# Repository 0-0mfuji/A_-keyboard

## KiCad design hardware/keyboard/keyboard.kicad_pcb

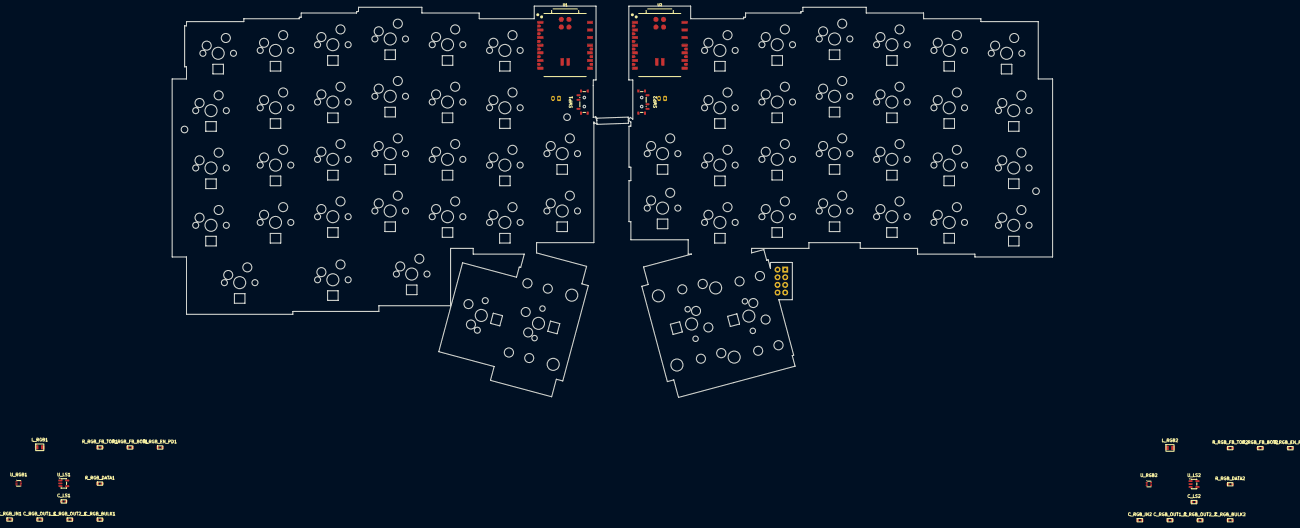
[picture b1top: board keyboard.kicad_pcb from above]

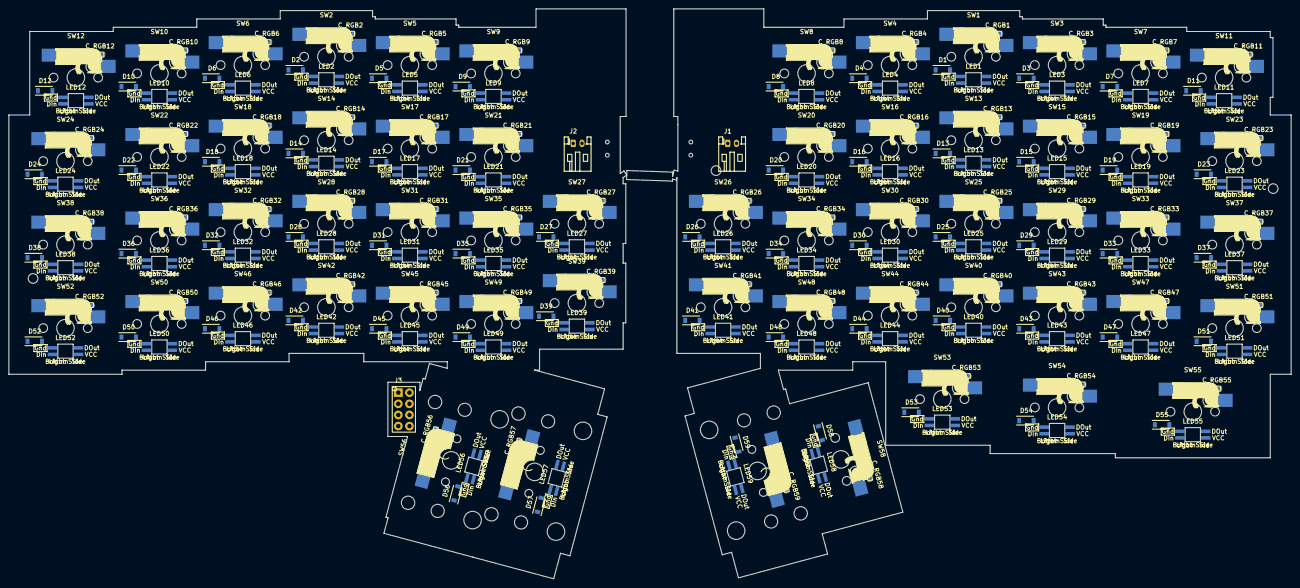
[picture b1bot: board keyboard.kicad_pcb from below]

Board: 2 copper layers, 292.5 x 130.0 mm, 276 parts (180 on the bottom side), 160 nets, no tracks yet.

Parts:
C_LS1, C_LS2: 100nF; C_0603
C_RGB1, C_RGB2, C_RGB3, C_RGB4, C_RGB5, C_RGB6, C_RGB7, C_RGB8, C_RGB9, C_RGB10, C_RGB11, C_RGB12, C_RGB13, C_RGB14, C_RGB15, C_RGB16, C_RGB17, C_RGB18, C_RGB19, C_RGB20, C_RGB21, C_RGB22, C_RGB23, C_RGB24, C_RGB25, C_RGB26, C_RGB27, C_RGB28, C_RGB29, C_RGB30, C_RGB31, C_RGB32, C_RGB33, C_RGB34, C_RGB35, C_RGB36, C_RGB37, C_RGB38, C_RGB39, C_RGB40, C_RGB41, C_RGB42, C_RGB43, C_RGB44, C_RGB45, C_RGB46, C_RGB47, C_RGB48, C_RGB49, C_RGB50, C_RGB51, C_RGB52, C_RGB53, C_RGB54, C_RGB55, C_RGB56, C_RGB57, C_RGB58, C_RGB59: 100nF; C_0603
C_RGB_BULK1, C_RGB_BULK2: 100uF; C_0603
C_RGB_IN1, C_RGB_IN2: 10uF; C_0603
C_RGB_OUT1_1, C_RGB_OUT1_2, C_RGB_OUT2_1, C_RGB_OUT2_2: 22uF; C_0603
D1, D2, D3, D4, D5, D6, D7, D8, D9, D10, D11, D12, D13, D14, D15, D16, D17, D18, D19, D20, D21, D22, D23, D24, D25, D26, D27, D28, D29, D30, D31, D32, D33, D34, D35, D36, D37, D38, D39, D40, D41, D42, D43, D44, D45, D46, D47, D48, D49, D50, D51, D52, D53, D54, D55, D56, D57, D58, D59: 1N4148W; SOD123
H: M2 NPTH clearance; MountingHole
H#2, H#3: M2 NPTH clearance; MountingHole
J1, J2: JST PH 2.0 2-pin; BatteryConnector_JST_PH2
J3: SEIBOKU / jumper wires; SEIBOKU_JUMPER_HEADER
LED1, LED2, LED3, LED4, LED5, LED6, LED7, LED8, LED9, LED10, LED11, LED12, LED13, LED14, LED15, LED16, LED17, LED18, LED19, LED20, LED21, LED22, LED23, LED24, LED25, LED26, LED27, LED28, LED29, LED30, LED31, LED32, LED33, LED34, LED35, LED36, LED37, LED38, LED39, LED40, LED41, LED42, LED43, LED44, LED45, LED46, LED47, LED48, LED49, LED50, LED51, LED52, LED53, LED54, LED55, LED56, LED57, LED58, LED59: SK6812MINI-E; LED_SK6812MINI-E_BL
L_RGB1, L_RGB2: 1uH; L_1008
R_RGB_DATA1, R_RGB_DATA2: 220R; R_0603
R_RGB_EN_PD1, R_RGB_EN_PD2: 100k; R_0603
R_RGB_FB_BOT1, R_RGB_FB_BOT2: 100k; R_0603
R_RGB_FB_TOP1, R_RGB_FB_TOP2: 732k; R_0603
STAB: MX stabilizer NPTH; MXStabilizerHole
STAB#2, STAB#3, STAB#4, STAB#5, STAB#6: MX stabilizer NPTH; MXStabilizerHole
SW1, SW2, SW3, SW4, SW5, SW6, SW7, SW8, SW9, SW10, SW11, SW12, SW13, SW14, SW15, SW16, SW17, SW18, SW19, SW20, SW21, SW22, SW25, SW26, SW27, SW28, SW29, SW30, SW31, SW32, SW33, SW34, SW35, SW36, SW39, SW40, SW41, SW42, SW43, SW44, SW45, SW46, SW47, SW48, SW49, SW50: MX; MX_Hotswap_1u
SW23, SW24, SW37, SW38, SW51, SW52, SW53: MX; MX_Hotswap_1.25u
SW54, SW58: MX; MX_Hotswap_1.5u
SW55: MX; MX_Hotswap_1.75u
SW56: MX; MX_Hotswap_2u
SW57, SW59: MX; MX_Hotswap_2.25u
SWP1, SWP2: MSK-12C02 slide switch; PowerSwitch_MSK12C02
U1, U2: XIAO nRF52840 Plus (SMD); XIAO_NRF52840_PLUS
U_LS1, U_LS2: SN74AHCT1G125
U_RGB1, U_RGB2: TPS61023

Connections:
+3V3_RIGHT: J3.1, U2.12
/COL0: SW1.1, SW8.1, SW16.1, SW25.1, SW33.1, SW41.1, SW48.1, SW55.1, U1.9
/COL1: SW3.1, SW11.1, SW19.1, SW26.1, SW34.1, SW43.1, SW51.1, SW58.1, U1.10
/COL2: SW4.1, SW13.1, SW20.1, SW29.1, SW37.1, SW44.1, SW53.1, SW59.1, U1.11
/COL3: SW7.1, SW15.1, SW23.1, SW30.1, SW40.1, SW47.1, SW54.1, U1.15
/COL4: SW6.1, SW14.1, SW22.1, SW31.1, SW38.1, SW46.1, SW56.1, U2.15
/COL5: SW9.1, SW17.1, SW24.1, SW32.1, SW39.1, SW49.1, SW57.1, U2.16
/COL6: SW2.1, SW10.1, SW18.1, SW27.1, SW35.1, SW42.1, SW50.1, U2.17
/COL7: SW5.1, SW12.1, SW21.1, SW28.1, SW36.1, SW45.1, SW52.1, U2.21
/GND_LEFT: C_LS1.2, C_RGB1.2, C_RGB3.2, C_RGB4.2, C_RGB7.2, C_RGB8.2, C_RGB11.2, C_RGB13.2, C_RGB15.2, C_RGB16.2, C_RGB19.2, C_RGB20.2, C_RGB23.2, C_RGB25.2, C_RGB26.2, C_RGB29.2, C_RGB30.2, C_RGB33.2, C_RGB34.2, C_RGB37.2, C_RGB40.2, C_RGB41.2, C_RGB43.2, C_RGB44.2, C_RGB47.2, C_RGB48.2, C_RGB51.2, C_RGB53.2, C_RGB54.2, C_RGB55.2, C_RGB58.2, C_RGB59.2, C_RGB_BULK1.2, C_RGB_IN1.2, C_RGB_OUT1_1.2, C_RGB_OUT2_1.2, J1.2, LED1.2, LED3.2, LED4.2, LED7.2, LED8.2, LED11.2, LED13.2, LED15.2, LED16.2, LED19.2, LED20.2, LED23.2, LED25.2, LED26.2, LED29.2, LED30.2, LED33.2, LED34.2, LED37.2, LED40.2, LED41.2, LED43.2, LED44.2, LED47.2, LED48.2, LED51.2, LED53.2, LED54.2, LED55.2, LED58.2, LED59.2, R_RGB_EN_PD1.2, R_RGB_FB_BOT1.2, U1.13, U1.27, U1.29, U_LS1.1, U_LS1.3, U_RGB1.4
/GND_RIGHT: C_LS2.2, C_RGB2.2, C_RGB5.2, C_RGB6.2, C_RGB9.2, C_RGB10.2, C_RGB12.2, C_RGB14.2, C_RGB17.2, C_RGB18.2, C_RGB21.2, C_RGB22.2, C_RGB24.2, C_RGB27.2, C_RGB28.2, C_RGB31.2, C_RGB32.2, C_RGB35.2, C_RGB36.2, C_RGB38.2, C_RGB39.2, C_RGB42.2, C_RGB45.2, C_RGB46.2, C_RGB49.2, C_RGB50.2, C_RGB52.2, C_RGB56.2, C_RGB57.2, C_RGB_BULK2.2, C_RGB_IN2.2, C_RGB_OUT1_2.2, C_RGB_OUT2_2.2, J2.2, J3.2, LED2.2, LED5.2, LED6.2, LED9.2, LED10.2, LED12.2, LED14.2, LED17.2, LED18.2, LED21.2, LED22.2, LED24.2, LED27.2, LED28.2, LED31.2, LED32.2, LED35.2, LED36.2, LED38.2, LED39.2, LED42.2, LED45.2, LED46.2, LED49.2, LED50.2, LED52.2, LED56.2, LED57.2, R_RGB_EN_PD2.2, R_RGB_FB_BOT2.2, U2.13, U2.27, U2.29, U_LS2.1, U_LS2.3, U_RGB2.4
/RGB_5V_LEFT: C_LS1.1, C_RGB1.1, C_RGB3.1, C_RGB4.1, C_RGB7.1, C_RGB8.1, C_RGB11.1, C_RGB13.1, C_RGB15.1, C_RGB16.1, C_RGB19.1, C_RGB20.1, C_RGB23.1, C_RGB25.1, C_RGB26.1, C_RGB29.1, C_RGB30.1, C_RGB33.1, C_RGB34.1, C_RGB37.1, C_RGB40.1, C_RGB41.1, C_RGB43.1, C_RGB44.1, C_RGB47.1, C_RGB48.1, C_RGB51.1, C_RGB53.1, C_RGB54.1, C_RGB55.1, C_RGB58.1, C_RGB59.1, C_RGB_BULK1.1, C_RGB_OUT1_1.1, C_RGB_OUT2_1.1, LED1.1, LED3.1, LED4.1, LED7.1, LED8.1, LED11.1, LED13.1, LED15.1, LED16.1, LED19.1, LED20.1, LED23.1, LED25.1, LED26.1, LED29.1, LED30.1, LED33.1, LED34.1, LED37.1, LED40.1, LED41.1, LED43.1, LED44.1, LED47.1, LED48.1, LED51.1, LED53.1, LED54.1, LED55.1, LED58.1, LED59.1, R_RGB_FB_TOP1.1, U_LS1.5, U_RGB1.6
/RGB_5V_RIGHT: C_LS2.1, C_RGB2.1, C_RGB5.1, C_RGB6.1, C_RGB9.1, C_RGB10.1, C_RGB12.1, C_RGB14.1, C_RGB17.1, C_RGB18.1, C_RGB21.1, C_RGB22.1, C_RGB24.1, C_RGB27.1, C_RGB28.1, C_RGB31.1, C_RGB32.1, C_RGB35.1, C_RGB36.1, C_RGB38.1, C_RGB39.1, C_RGB42.1, C_RGB45.1, C_RGB46.1, C_RGB49.1, C_RGB50.1, C_RGB52.1, C_RGB56.1, C_RGB57.1, C_RGB_BULK2.1, C_RGB_OUT1_2.1, C_RGB_OUT2_2.1, LED2.1, LED5.1, LED6.1, LED9.1, LED10.1, LED12.1, LED14.1, LED17.1, LED18.1, LED21.1, LED22.1, LED24.1, LED27.1, LED28.1, LED31.1, LED32.1, LED35.1, LED36.1, LED38.1, LED39.1, LED42.1, LED45.1, LED46.1, LED49.1, LED50.1, LED52.1, LED56.1, LED57.1, R_RGB_FB_TOP2.1, U_LS2.5, U_RGB2.6
/RGB_DATA_LEFT: U1.16, U_LS1.2
/RGB_DATA_RIGHT: U2.22, U_LS2.2
/RGB_DATA_SHIFTED_LEFT: LED1.3, R_RGB_DATA1.2
/RGB_DATA_SHIFTED_RIGHT: LED2.3, R_RGB_DATA2.2
/RGB_EN_LEFT: R_RGB_EN_PD1.1, U1.17, U_RGB1.2
/RGB_EN_RIGHT: R_RGB_EN_PD2.1, U2.23, U_RGB2.2
/ROW0: D1.1, D3.1, D4.1, D7.1, U1.1
/ROW1: D8.1, D11.1, D13.1, D15.1, U1.2
/ROW2: D16.1, D19.1, D20.1, D23.1, U1.3
/ROW3: D25.1, D26.1, D29.1, D30.1, U1.4
/ROW4: D33.1, D34.1, D37.1, D40.1, U1.5
/ROW5: D41.1, D43.1, D44.1, D47.1, U1.6
/ROW6: D48.1, D51.1, D53.1, D54.1, U1.7
/ROW7: D55.1, D58.1, D59.1, U1.8
/ROW8: D2.1, D5.1, D56.1, D57.1, U2.3
/ROW9: D6.1, D9.1, D10.1, D12.1, U2.4
/ROW10: D14.1, D17.1, D18.1, D21.1, U2.5
/ROW11: D22.1, D24.1, D27.1, D28.1, U2.6
/ROW12: D31.1, D32.1, D35.1, D36.1, U2.7
/ROW13: D38.1, D39.1, D42.1, D45.1, U2.8
/ROW14: D46.1, D49.1, D50.1, D52.1, U2.10
/VBAT_LEFT: C_RGB_IN1.1, L_RGB1.1, SWP1.2, U1.28, U_RGB1.3
/VBAT_RIGHT: C_RGB_IN2.1, L_RGB2.1, SWP2.2, U2.28, U_RGB2.3
/matrix/SW1_A: D1.2, SW1.2
/matrix/SW2_A: D2.2, SW2.2
/matrix/SW3_A: D3.2, SW3.2
/matrix/SW4_A: D4.2, SW4.2
/matrix/SW5_A: D5.2, SW5.2
/matrix/SW6_A: D6.2, SW6.2
/matrix/SW7_A: D7.2, SW7.2
/matrix/SW8_A: D8.2, SW8.2
/matrix/SW9_A: D9.2, SW9.2
/matrix/SW10_A: D10.2, SW10.2
/matrix/SW11_A: D11.2, SW11.2
/matrix/SW12_A: D12.2, SW12.2
/matrix/SW13_A: D13.2, SW13.2
/matrix/SW14_A: D14.2, SW14.2
/matrix/SW15_A: D15.2, SW15.2
/matrix/SW16_A: D16.2, SW16.2
/matrix/SW17_A: D17.2, SW17.2
/matrix/SW18_A: D18.2, SW18.2
/matrix/SW19_A: D19.2, SW19.2
/matrix/SW20_A: D20.2, SW20.2
/matrix/SW21_A: D21.2, SW21.2
/matrix/SW22_A: D22.2, SW22.2
/matrix/SW23_A: D23.2, SW23.2
/matrix/SW24_A: D24.2, SW24.2
/matrix/SW25_A: D25.2, SW25.2
/matrix/SW26_A: D26.2, SW26.2
/matrix/SW27_A: D27.2, SW27.2
/matrix/SW28_A: D28.2, SW28.2
/matrix/SW29_A: D29.2, SW29.2
/matrix/SW30_A: D30.2, SW30.2
/matrix/SW31_A: D31.2, SW31.2
/matrix/SW32_A: D32.2, SW32.2
/matrix/SW33_A: D33.2, SW33.2
/matrix/SW34_A: D34.2, SW34.2
/matrix/SW35_A: D35.2, SW35.2
/matrix/SW36_A: D36.2, SW36.2
/matrix/SW37_A: D37.2, SW37.2
/matrix/SW38_A: D38.2, SW38.2
/matrix/SW39_A: D39.2, SW39.2
/matrix/SW40_A: D40.2, SW40.2
/matrix/SW41_A: D41.2, SW41.2
/matrix/SW42_A: D42.2, SW42.2
/matrix/SW43_A: D43.2, SW43.2
/matrix/SW44_A: D44.2, SW44.2
/matrix/SW45_A: D45.2, SW45.2
/matrix/SW46_A: D46.2, SW46.2
/matrix/SW47_A: D47.2, SW47.2
/matrix/SW48_A: D48.2, SW48.2
/matrix/SW49_A: D49.2, SW49.2
/matrix/SW50_A: D50.2, SW50.2
/matrix/SW51_A: D51.2, SW51.2
/matrix/SW52_A: D52.2, SW52.2
/matrix/SW53_A: D53.2, SW53.2
/matrix/SW54_A: D54.2, SW54.2
/matrix/SW55_A: D55.2, SW55.2
/matrix/SW56_A: D56.2, SW56.2
/matrix/SW57_A: D57.2, SW57.2
/matrix/SW58_A: D58.2, SW58.2
/matrix/SW59_A: D59.2, SW59.2
/power/BAT_RAW_LEFT: J1.1, SWP1.1
/power/BAT_RAW_RIGHT: J2.1, SWP2.1
/power/RGB_FB_LEFT: R_RGB_FB_BOT1.1, R_RGB_FB_TOP1.2, U_RGB1.1
/power/RGB_FB_RIGHT: R_RGB_FB_BOT2.1, R_RGB_FB_TOP2.2, U_RGB2.1
/power/RGB_SHIFTED_LEFT: R_RGB_DATA1.1, U_LS1.4
/power/RGB_SHIFTED_RIGHT: R_RGB_DATA2.1, U_LS2.4
/power/RGB_SW_LEFT: L_RGB1.2, U_RGB1.5
/power/RGB_SW_RIGHT: L_RGB2.2, U_RGB2.5
/rgb/RGB_LED_left_0: LED1.4, LED3.3
/rgb/RGB_LED_left_1: LED3.4, LED4.3
/rgb/RGB_LED_left_2: LED4.4, LED7.3
/rgb/RGB_LED_left_3: LED7.4, LED8.3
/rgb/RGB_LED_left_4: LED8.4, LED11.3
/rgb/RGB_LED_left_5: LED11.4, LED13.3
/rgb/RGB_LED_left_6: LED13.4, LED15.3
/rgb/RGB_LED_left_7: LED15.4, LED16.3
/rgb/RGB_LED_left_8: LED16.4, LED19.3
/rgb/RGB_LED_left_9: LED19.4, LED20.3
/rgb/RGB_LED_left_10: LED20.4, LED23.3
/rgb/RGB_LED_left_11: LED23.4, LED25.3
/rgb/RGB_LED_left_12: LED25.4, LED26.3
/rgb/RGB_LED_left_13: LED26.4, LED29.3
/rgb/RGB_LED_left_14: LED29.4, LED30.3
/rgb/RGB_LED_left_15: LED30.4, LED33.3
/rgb/RGB_LED_left_16: LED33.4, LED34.3
/rgb/RGB_LED_left_17: LED34.4, LED37.3
/rgb/RGB_LED_left_18: LED37.4, LED40.3
/rgb/RGB_LED_left_19: LED40.4, LED41.3
/rgb/RGB_LED_left_20: LED41.4, LED43.3
/rgb/RGB_LED_left_21: LED43.4, LED44.3
/rgb/RGB_LED_left_22: LED44.4, LED47.3
/rgb/RGB_LED_left_23: LED47.4, LED48.3
/rgb/RGB_LED_left_24: LED48.4, LED51.3
/rgb/RGB_LED_left_25: LED51.4, LED53.3
/rgb/RGB_LED_left_26: LED53.4, LED54.3
/rgb/RGB_LED_left_27: LED54.4, LED55.3
/rgb/RGB_LED_left_28: LED55.4, LED58.3
/rgb/RGB_LED_left_29: LED58.4, LED59.3
/rgb/RGB_LED_right_0: LED2.4, LED5.3
/rgb/RGB_LED_right_1: LED5.4, LED6.3
/rgb/RGB_LED_right_2: LED6.4, LED9.3
/rgb/RGB_LED_right_3: LED9.4, LED10.3
/rgb/RGB_LED_right_4: LED10.4, LED12.3
/rgb/RGB_LED_right_5: LED12.4, LED14.3
/rgb/RGB_LED_right_6: LED14.4, LED17.3
/rgb/RGB_LED_right_7: LED17.4, LED18.3
/rgb/RGB_LED_right_8: LED18.4, LED21.3
/rgb/RGB_LED_right_9: LED21.4, LED22.3
/rgb/RGB_LED_right_10: LED22.4, LED24.3
/rgb/RGB_LED_right_11: LED24.4, LED27.3
/rgb/RGB_LED_right_12: LED27.4, LED28.3
/rgb/RGB_LED_right_13: LED28.4, LED31.3
/rgb/RGB_LED_right_14: LED31.4, LED32.3
/rgb/RGB_LED_right_15: LED32.4, LED35.3
/rgb/RGB_LED_right_16: LED35.4, LED36.3
/rgb/RGB_LED_right_17: LED36.4, LED38.3
/rgb/RGB_LED_right_18: LED38.4, LED39.3
/rgb/RGB_LED_right_19: LED39.4, LED42.3
/rgb/RGB_LED_right_20: LED42.4, LED45.3
/rgb/RGB_LED_right_21: LED45.4, LED46.3
/rgb/RGB_LED_right_22: LED46.4, LED49.3
/rgb/RGB_LED_right_23: LED49.4, LED50.3
/rgb/RGB_LED_right_24: LED50.4, LED52.3
/rgb/RGB_LED_right_25: LED52.4, LED56.3
/rgb/RGB_LED_right_26: LED56.4, LED57.3

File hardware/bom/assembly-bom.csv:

Designator,Quantity,Value,Footprint,MPN,LCSC Part Number,Assembly
"D1 D2 D3 D4 D5 D6 D7 D8 D9 D10 D11 D12 D13 D14 D15 D16 D17 D18 D19 D20 D21 D22 D23 D24 D25 D26 D27 D28 D29 D30 D31 D32 D33 D34 D35 D36 D37 D38 D39 D40 D41 D42 D43 D44 D45 D46 D47 D48 D49 D50 D51 D52 D53 D54 D55 D56 D57 D58 D59","59","1N4148W","Keyboard:SOD123","","","smt"
"LED1 LED2 LED3 LED4 LED5 LED6 LED7 LED8 LED9 LED10 LED11 LED12 LED13 LED14 LED15 LED16 LED17 LED18 LED19 LED20 LED21 LED22 LED23 LED24 LED25 LED26 LED27 LED28 LED29 LED30 LED31 LED32 LED33 LED34 LED35 LED36 LED37 LED38 LED39 LED40 LED41 LED42 LED43 LED44 LED45 LED46 LED47 LED48 LED49 LED50 LED51 LED52 LED53 LED54 LED55 LED56 LED57 LED58 LED59","59","SK6812MINI-E","Keyboard:LED_SK6812MINI-E_BL","","","smt"
"C_RGB1 C_RGB2 C_RGB3 C_RGB4 C_RGB5 C_RGB6 C_LS1 C_LS2 C_RGB7 C_RGB8 C_RGB9 C_RGB10 C_RGB11 C_RGB12 C_RGB13 C_RGB14 C_RGB15 C_RGB16 C_RGB17 C_RGB18 C_RGB19 C_RGB20 C_RGB21 C_RGB22 C_RGB23 C_RGB24 C_RGB25 C_RGB26 C_RGB27 C_RGB28 C_RGB29 C_RGB30 C_RGB31 C_RGB32 C_RGB33 C_RGB34 C_RGB35 C_RGB36 C_RGB37 C_RGB38 C_RGB39 C_RGB40 C_RGB41 C_RGB42 C_RGB43 C_RGB44 C_RGB45 C_RGB46 C_RGB47 C_RGB48 C_RGB49 C_RGB50 C_RGB51 C_RGB52 C_RGB53 C_RGB54 C_RGB55 C_RGB56 C_RGB57 C_RGB58 C_RGB59","61","100nF","Keyboard:C_0603","","","smt"
"U1 U2","2","XIAO nRF52840 Plus (SMD)","Keyboard:XIAO_NRF52840_PLUS","","","smt"
"U_RGB1 U_RGB2","2","TPS61023","Keyboard:TPS61023","","","smt"
"C_RGB_BULK1 C_RGB_BULK2","2","100uF","Keyboard:C_0603","","","smt"
"C_RGB_IN1 C_RGB_IN2","2","10uF","Keyboard:C_0603","","","smt"
"C_RGB_OUT1_1 C_RGB_OUT2_1 C_RGB_OUT1_2 C_RGB_OUT2_2","4","22uF","Keyboard:C_0603","","","smt"
"R_RGB_DATA1 R_RGB_DATA2","2","220R","Keyboard:R_0603","","","smt"
"R_RGB_EN_PD1 R_RGB_FB_BOT1 R_RGB_EN_PD2 R_RGB_FB_BOT2","4","100k","Keyboard:R_0603","","","smt"
"L_RGB1 L_RGB2","2","1uH","Keyboard:L_1008","","","smt"
"U_LS1 U_LS2","2","SN74AHCT1G125","Keyboard:SN74AHCT1G125","","","smt"
"R_RGB_FB_TOP1 R_RGB_FB_TOP2","2","732k","Keyboard:R_0603","","","smt"
"SWP1 SWP2","2","MSK-12C02 slide switch","Keyboard:PowerSwitch_MSK12C02","","","smt"
